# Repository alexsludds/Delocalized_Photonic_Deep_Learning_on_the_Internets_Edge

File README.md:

<div id="top"></div>

<!-- PROJECT LOGO -->
<br />

<h3 align="center">Delocalized Photonic Deep Learning on the Internet's Edge</h3>

  <p align="justify">
    Code and data for paper "Delocalized Photonic Deep Learning on the Internet's Edge", preprint available on <a href="https://arxiv.org/abs/2203.05466">arXiv</a>. If you use methods in this repository or find them useful, please cite our work.
    <br />
  </p>
</div>

<!-- ABOUT THE PROJECT -->
## About

This repository contains codes and data published in the above-mentioned manuscript. The code presented here allow for the analysis of laboratory data that was taken for the creation of figuers in the paper.

<ul>
  <li>Numerical simulation of Netcast under thermal and shot noise regimes</li>        
  <li>Analysis of experimental data from time-integrating detectors, APDs and SNSPDs </li>
  <li>Project files for creating custom time-integrating receivers.</li>        
</ul>

<p align="right">(<a href="#top">back to top</a>)</p>

<!-- GETTING STARTED -->
## Getting Started

To get a local copy up and running follow these simple example steps.

### Installation

Clone the repository

### Python Prerequisites

Python sections of the code were written in Python 3.9.6. To download required Python packages, you can use the following command (preferably in a virtual environment):
* Python Requirements
  ```sh
  pip install -r requirements.txt
  ```

<p align="right">(<a href="#top">back to top</a>)</p>

<!-- CONTACT -->
## Contact

All questions, inquiries, or suggestions should be addressed to the corresponding authors of the manuscript:

* Alex Sludds - [@personal_website](https://alexsludds.github.io/) - asludds@mit.edu

<p align="right">(<a href="#top">back to top</a>)</p>

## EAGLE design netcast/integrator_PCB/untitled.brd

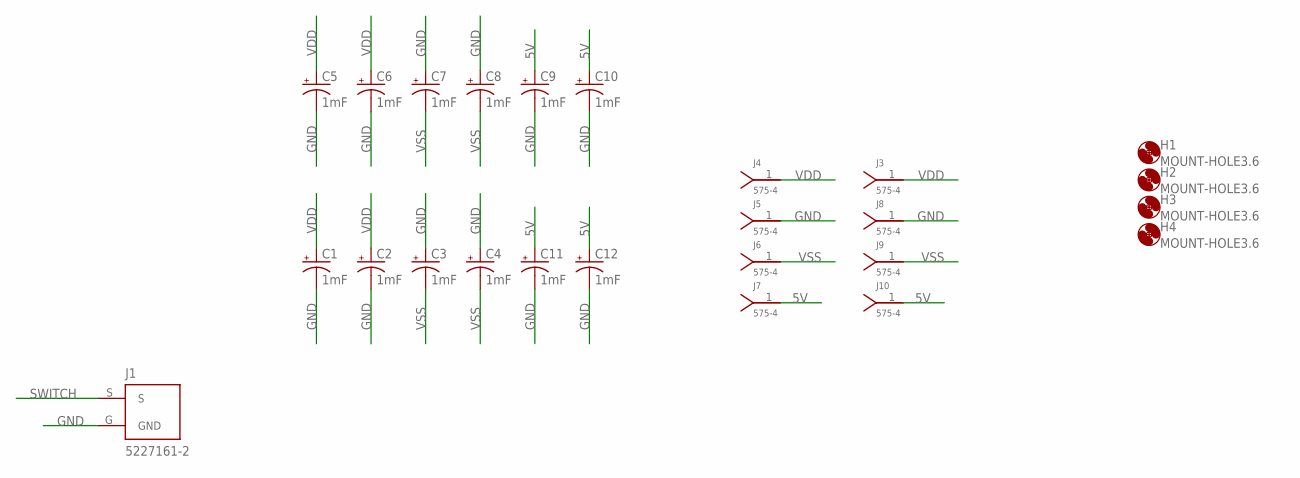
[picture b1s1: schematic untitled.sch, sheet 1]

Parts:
C1, C2, C3, C4, C5, C6, C7, C8, C9, C10, C11, C12: 1mF; CPOL-RADIAL-5MM-10MM
H1, H2, H3, H4: MOUNT-HOLE3.6; 3,6
J1: 5227161-2; TE_5227161-2
J3, J4, J5, J6, J7, J8, J9, J10: 575-4; KEYSTONE_575-4

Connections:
5V: C9.+, C10.+, C11.+, C12.+, J7.1, J10.1; also elsewhere on the board
GND: C1.-, C2.-, C3.+, C4.+, C5.-, C6.-, C7.+, C8.+, C9.-, C10.-, C11.-, C12.-, J1.G (GND), J5.1, J8.1; also elsewhere on the board
SWITCH: J1.S; also elsewhere on the board
VDD: C1.+, C2.+, C5.+, C6.+, J3.1, J4.1; also elsewhere on the board
VSS: C3.-, C4.-, C7.-, C8.-, J6.1, J9.1; also elsewhere on the board

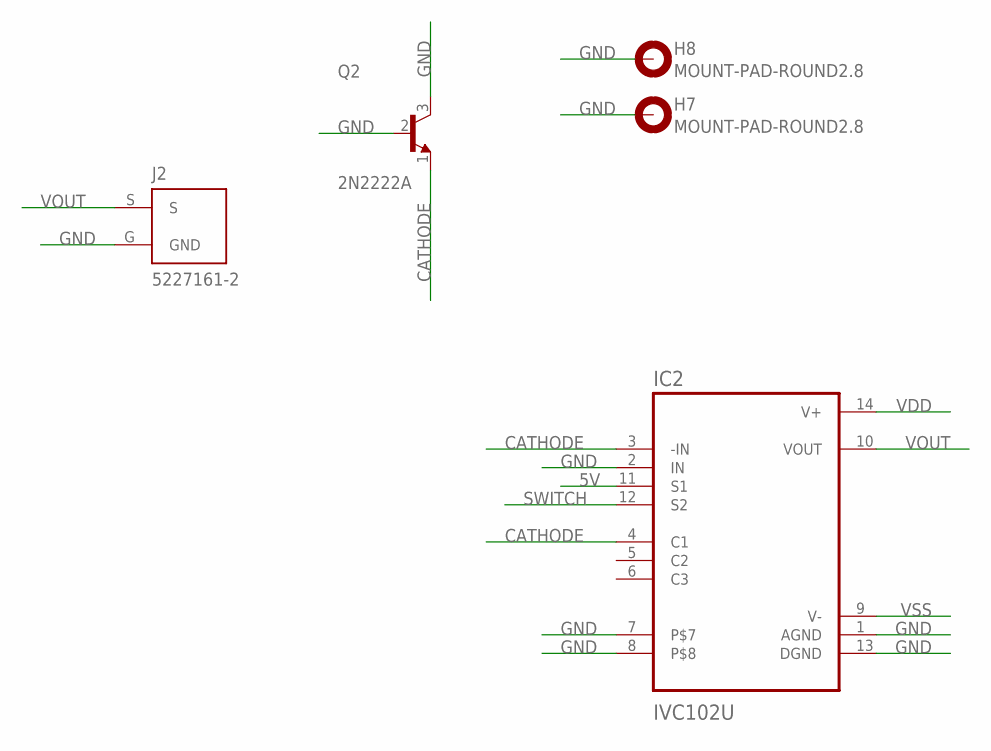
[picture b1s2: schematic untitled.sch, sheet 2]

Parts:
H7, H8: MOUNT-PAD-ROUND2.8; 2,8-PAD
IC2: IVC102U; SOIC127P600X175-14N
J2: 5227161-2; TE_5227161-2
Q2: 2N2222A; TO127P584H533-3

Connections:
5V: IC2.11 (S1); also elsewhere on the board
CATHODE: IC2.3 (-IN), IC2.4 (C1), Q2.1 (E)
GND: H7.B2,8, H8.B2,8, IC2.1 (AGND), IC2.2 (IN), IC2.7, IC2.8, IC2.13 (DGND), J2.G (GND), Q2.2 (B), Q2.3 (C); also elsewhere on the board
SWITCH: IC2.12 (S2); also elsewhere on the board
VDD: IC2.14 (V+); also elsewhere on the board
VOUT: IC2.10 (VOUT), J2.S
VSS: IC2.9 (V-); also elsewhere on the board

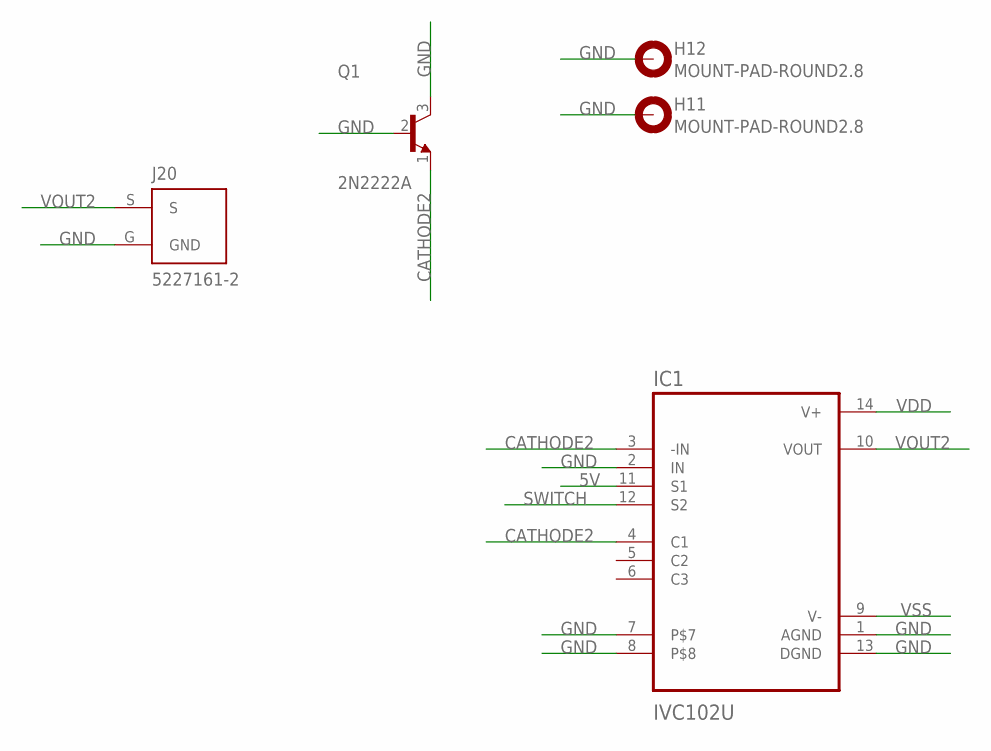
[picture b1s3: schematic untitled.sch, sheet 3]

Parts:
H11, H12: MOUNT-PAD-ROUND2.8; 2,8-PAD
IC1: IVC102U; SOIC127P600X175-14N
J20: 5227161-2; TE_5227161-2
Q1: 2N2222A; TO127P584H533-3

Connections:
5V: IC1.11 (S1); also elsewhere on the board
CATHODE2: IC1.3 (-IN), IC1.4 (C1), Q1.1 (E)
GND: H11.B2,8, H12.B2,8, IC1.1 (AGND), IC1.2 (IN), IC1.7, IC1.8, IC1.13 (DGND), J20.G (GND), Q1.2 (B), Q1.3 (C); also elsewhere on the board
SWITCH: IC1.12 (S2); also elsewhere on the board
VDD: IC1.14 (V+); also elsewhere on the board
VOUT2: IC1.10 (VOUT), J20.S
VSS: IC1.9 (V-); also elsewhere on the board

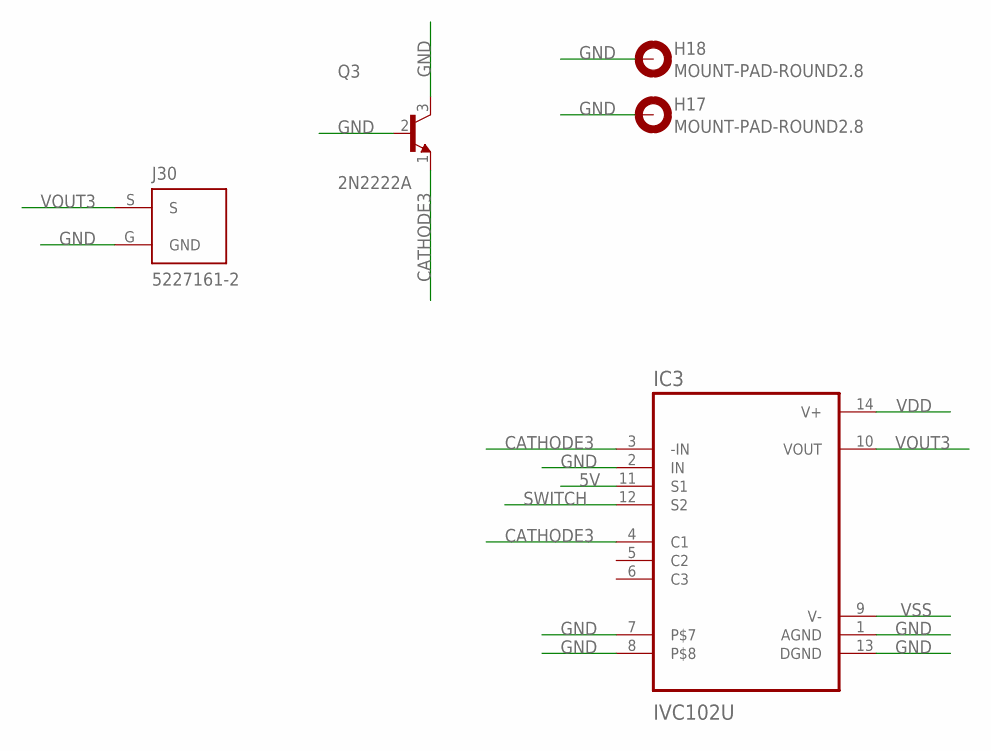
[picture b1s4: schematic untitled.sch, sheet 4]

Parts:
H17, H18: MOUNT-PAD-ROUND2.8; 2,8-PAD
IC3: IVC102U; SOIC127P600X175-14N
J30: 5227161-2; TE_5227161-2
Q3: 2N2222A; TO127P584H533-3

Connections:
5V: IC3.11 (S1); also elsewhere on the board
CATHODE3: IC3.3 (-IN), IC3.4 (C1), Q3.1 (E)
GND: H17.B2,8, H18.B2,8, IC3.1 (AGND), IC3.2 (IN), IC3.7, IC3.8, IC3.13 (DGND), J30.G (GND), Q3.2 (B), Q3.3 (C); also elsewhere on the board
SWITCH: IC3.12 (S2); also elsewhere on the board
VDD: IC3.14 (V+); also elsewhere on the board
VOUT3: IC3.10 (VOUT), J30.S
VSS: IC3.9 (V-); also elsewhere on the board

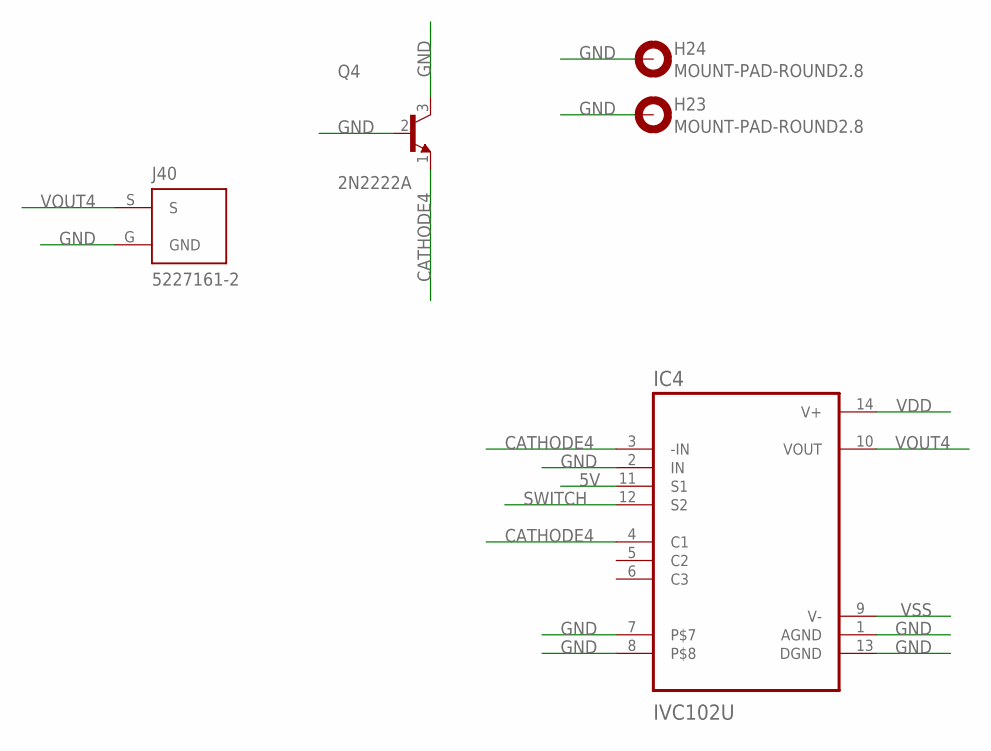
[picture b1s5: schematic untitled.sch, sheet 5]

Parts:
H23, H24: MOUNT-PAD-ROUND2.8; 2,8-PAD
IC4: IVC102U; SOIC127P600X175-14N
J40: 5227161-2; TE_5227161-2
Q4: 2N2222A; TO127P584H533-3

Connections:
5V: IC4.11 (S1); also elsewhere on the board
CATHODE4: IC4.3 (-IN), IC4.4 (C1), Q4.1 (E)
GND: H23.B2,8, H24.B2,8, IC4.1 (AGND), IC4.2 (IN), IC4.7, IC4.8, IC4.13 (DGND), J40.G (GND), Q4.2 (B), Q4.3 (C); also elsewhere on the board
SWITCH: IC4.12 (S2); also elsewhere on the board
VDD: IC4.14 (V+); also elsewhere on the board
VOUT4: IC4.10 (VOUT), J40.S
VSS: IC4.9 (V-); also elsewhere on the board

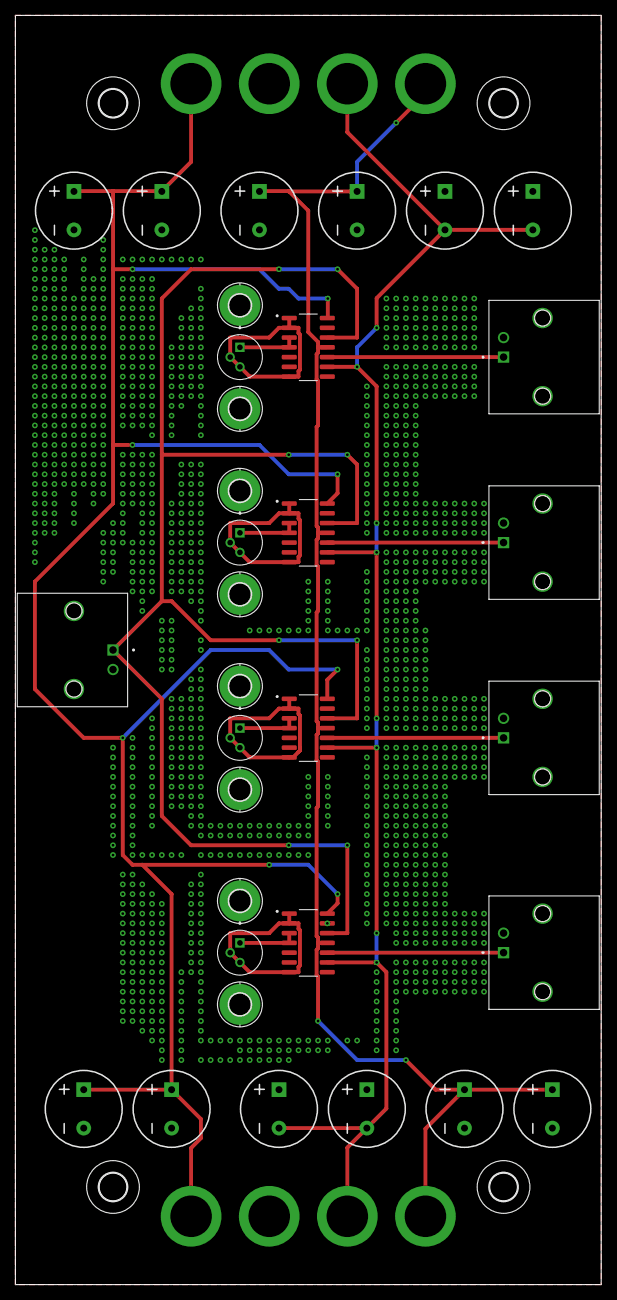
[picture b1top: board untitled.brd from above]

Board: 2 copper layers, 76.2 x 165.1 mm, 45 parts (0 on the bottom side), 13 nets.

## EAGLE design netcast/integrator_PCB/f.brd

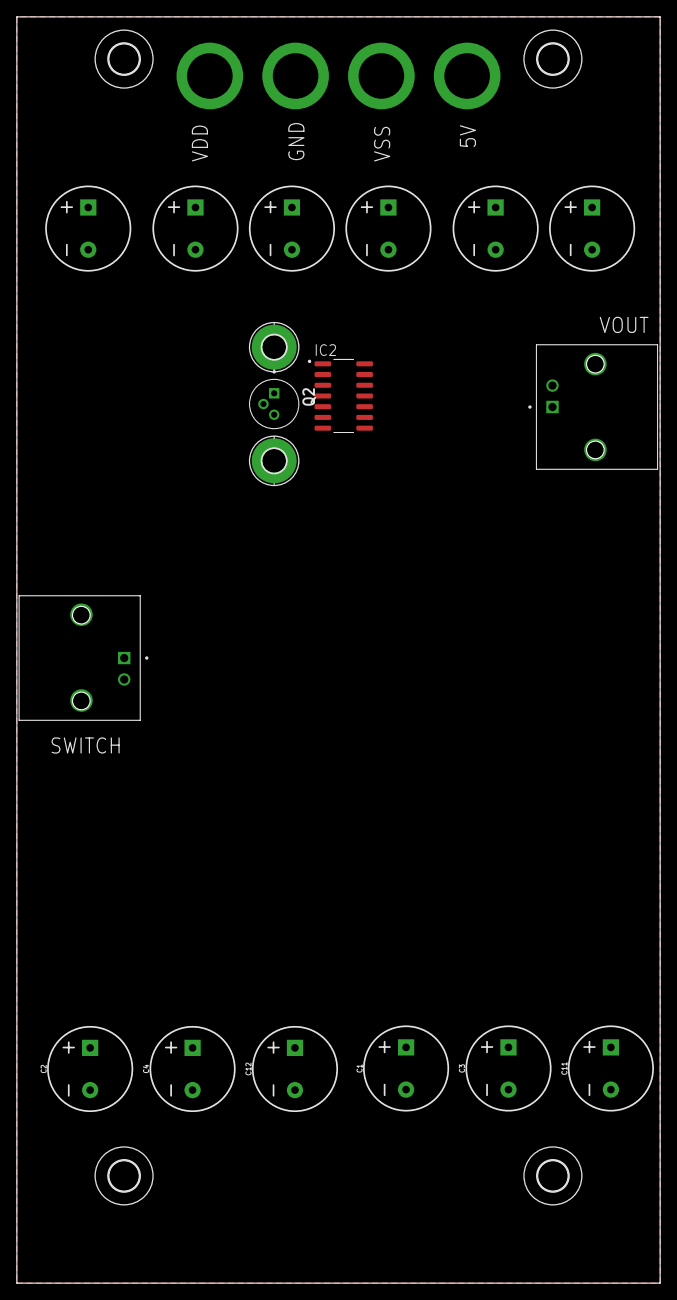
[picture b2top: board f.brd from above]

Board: 2 copper layers, 76.2 x 150.0 mm, 26 parts (0 on the bottom side), 11 nets, no tracks yet.

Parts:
C1, C2, C3, C4, C5, C6, C7, C8, C9, C10, C11, C12: 1mF; CPOL-RADIAL-5MM-10MM
H1, H2, H3, H4: MOUNT-HOLE3.6; 3,6
H7, H8: MOUNT-PAD-ROUND2.8; 2,8-PAD
IC2: IVC102U; SOIC127P600X175-14N
J3, J8: 5227161-2; TE_5227161-2
J4, J5, J6, J7: 575-4; KEYSTONE_575-4
Q2: 2N2222A; TO127P584H533-3

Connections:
5V: C11.+, C12.+, IC2.11
CATHODE1: IC2.3, IC2.4, Q2.1
GND: C1.-, C2.-, C3.+, C4.+, C11.-, C12.-, J3.G, J8.G
S$1: C5.-, C6.-, C7.+, C8.+, C9.-, C10.-, H7.B2,8, H8.B2,8, IC2.1, IC2.2, IC2.7, IC2.8, IC2.13, J5.1, Q2.2, Q2.3
S$4: C5.+, C6.+, J4.1
S$5: C7.-, C8.-, J6.1
S$7: C9.+, C10.+, J7.1
SWITCH: IC2.12, J3.S
VDD: C1.+, C2.+, IC2.14
VOUT1: IC2.10, J8.S
VSS: C3.-, C4.-, IC2.9

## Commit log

2022-08-11 Initial upload
2022-08-11 Removed README.md table of contents

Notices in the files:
parts and their libraries:
SparkFun-Capacitors: Licensing: Creative Commons ShareAlike 4.0 International - https://creativecommons.org/licenses/by-sa/4.0
